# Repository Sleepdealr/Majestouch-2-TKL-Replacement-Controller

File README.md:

# Majestouch 2 TKL Replacement Controller

This board has been prototyped. It is tested and working

Kicad source files are provided, as well as QMK firmware with Vial support

## Resources Used

- Matrix: <https://deskthority.net/wiki/Controller_matrix_traces#Filco_Majestouch_TKL>
- Outline: <https://github.com/Tecsmith/flying-horse-foot/>
  - Used calipers to double check with physical model

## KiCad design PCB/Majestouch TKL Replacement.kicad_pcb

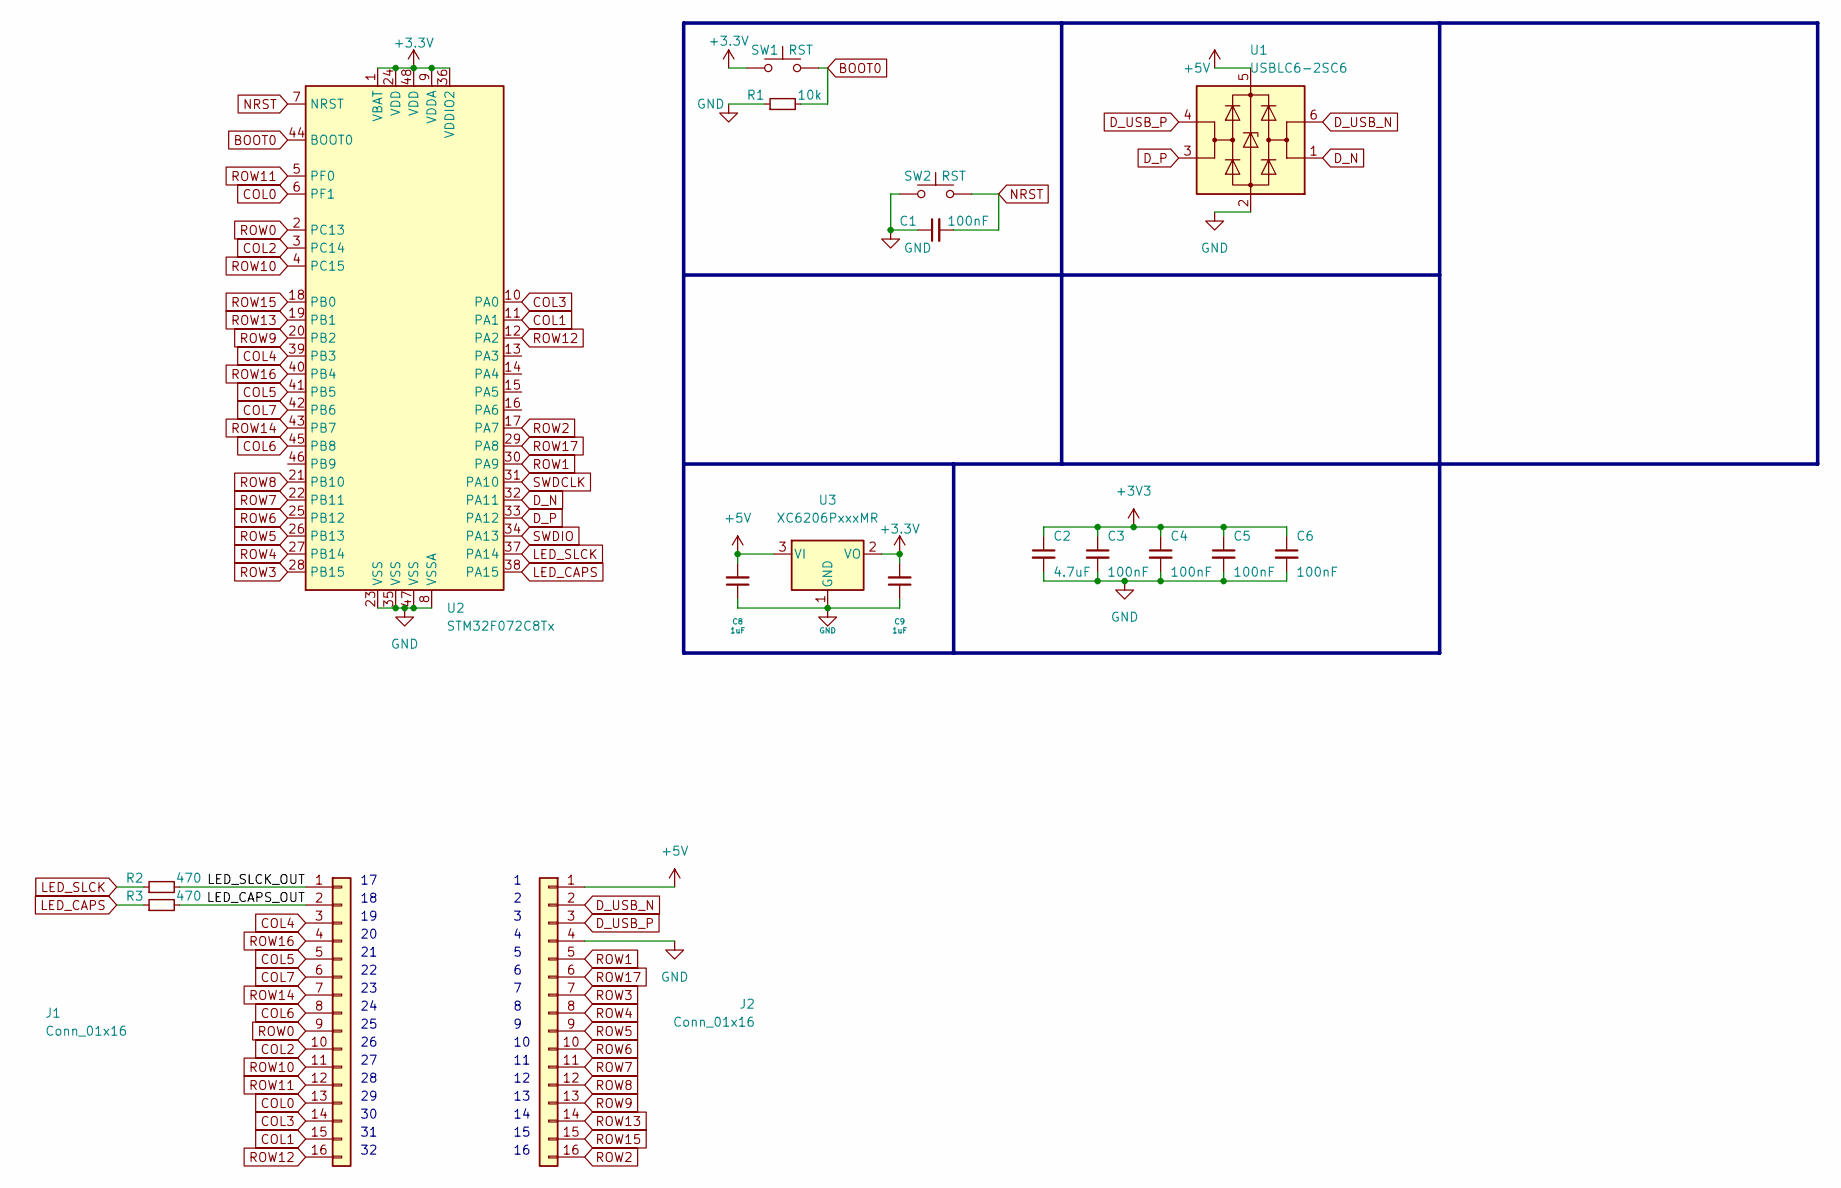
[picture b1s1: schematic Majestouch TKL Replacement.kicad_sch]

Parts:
C1, C3, C4, C5, C6: 100nF; C_0402_1005Metric; LCSC C307331
C2: 4.7uF; C_0402_1005Metric; LCSC C52923
C8, C9: 1uF; C_0402_1005Metric; LCSC C52923
J1, J2: Conn_01x16; PinHeader_1x16_P2.00mm_Vertical
R1: 10k; R_0402_1005Metric
R2, R3: 470; R_0402_1005Metric
SW1, SW2: RST; PinSocket_1x02_P2.54mm_Vertical
U1: USBLC6-2SC6; SOT-23-6
U2: STM32F072C8Tx; LQFP-48_7x7mm_P0.5mm
U3: XC6206PxxxMR; SOT-23

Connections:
+5V: C8.2, J2.1, U1.5 (VBUS), U3.3 (VI)
/LED_CAPS_OUT: J1.2, R3.2
/LED_SLCK_OUT: J1.1, R2.2
BOOT0: R1.2, SW1.2, U2.44 (BOOT0)
COL0: J1.13, U2.6 (PF1)
COL1: J1.15, U2.11 (PA1)
COL2: J1.10, U2.3 (PC14)
COL3: J1.14, U2.10 (PA0)
COL4: J1.3, U2.39 (PB3)
COL5: J1.5, U2.41 (PB5)
COL6: J1.8, U2.45 (PB8)
COL7: J1.6, U2.42 (PB6)
D_N: U1.1 (I/O1), U2.32 (PA11)
D_P: U1.3 (I/O2), U2.33 (PA12)
D_USB_N: J2.2, U1.6 (I/O1)
D_USB_P: J2.3, U1.4 (I/O2)
GND: C1.1, C2.2, C3.2, C4.2, C5.2, C6.2, C8.1, C9.1, J2.4, R1.1, SW2.1, U1.2 (GND), U2.8 (VSSA), U2.23 (VSS), U2.35 (VSS), U2.47 (VSS), U3.1 (GND)
LED_CAPS: R3.1, U2.38 (PA15)
LED_SLCK: R2.1, U2.37 (PA14)
NRST: C1.2, SW2.2, U2.7 (NRST)
ROW0: J1.9, U2.2 (PC13)
ROW1: J2.5, U2.30 (PA9)
ROW2: J2.16, U2.17 (PA7)
ROW3: J2.7, U2.28 (PB15)
ROW4: J2.8, U2.27 (PB14)
ROW5: J2.9, U2.26 (PB13)
ROW6: J2.10, U2.25 (PB12)
ROW7: J2.11, U2.22 (PB11)
ROW8: J2.12, U2.21 (PB10)
ROW9: J2.13, U2.20 (PB2)
ROW10: J1.11, U2.4 (PC15)
ROW11: J1.12, U2.5 (PF0)
ROW12: J1.16, U2.12 (PA2)
ROW13: J2.14, U2.19 (PB1)
ROW14: J1.7, U2.43 (PB7)
ROW15: J2.15, U2.18 (PB0)
ROW16: J1.4, U2.40 (PB4)
ROW17: J2.6, U2.29 (PA8)
SWDCLK: U2.31 (PA10)
SWDIO: U2.34 (PA13)

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
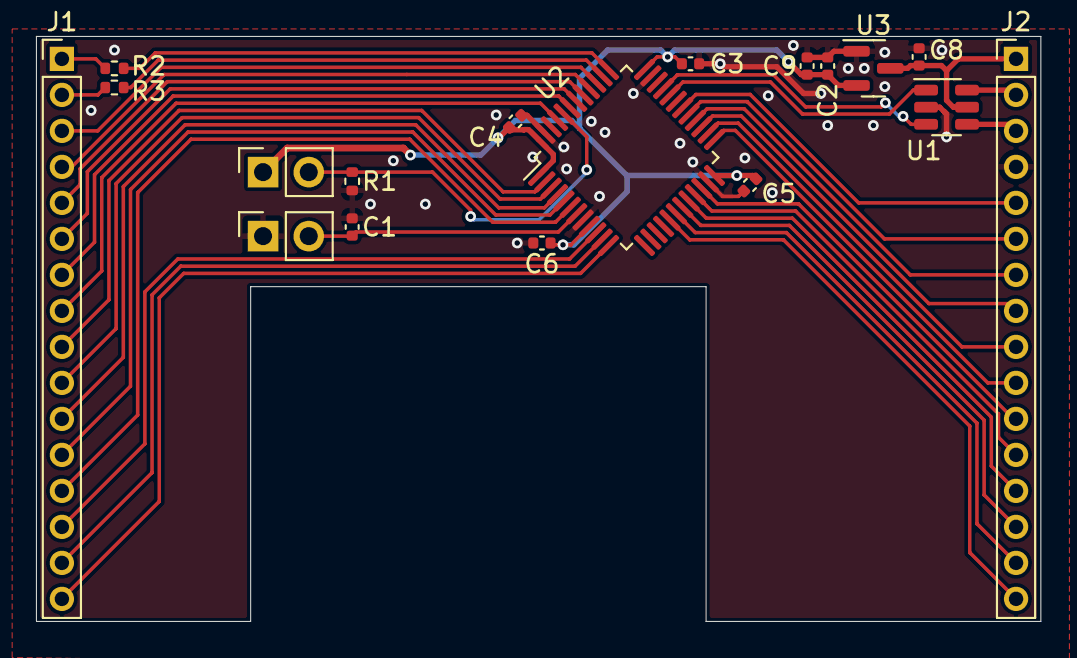
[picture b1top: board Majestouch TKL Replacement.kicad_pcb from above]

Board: 2 copper layers, 55.8 x 32.5 mm, 18 parts (0 on the bottom side), 39 nets.

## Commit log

2022-12-25 Init
